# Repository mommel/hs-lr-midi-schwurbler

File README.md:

# Der Schwurbler

Happy Shooting Community - DIY Lightroom Hardware Controller

## Description
The german foto podcast legend Happy Shooting had a discussion about Midi controller for Lightroom. One comment on the website and voila a new project is born.
This project will (hopefully) contain everything from zero to hero to get create your own customized Midi Controller for Lightroom.
It is completly community driven, so everyone is allowed to contribute. And it's not intended to earn money with it. Just from the community for the community.
In general you might even need no case, just the pcb with the solded parts. so you will get an extra small extra lightwight device. If that's the thing for you we might even go the capacitive way and reduce the soldered components and weight to a minimum.

## MVP Video

<object width="425" height="350">
  <param name="movie" value="https://youtu.be/SjJDIjGQ-qA" />
  <param name="wmode" value="transparent" />
  <embed src="https://youtu.be/SjJDIjGQ-qA"
         type="application/x-shockwave-flash"
         wmode="transparent" width="425" height="350" />
</object>

https://youtu.be/SjJDIjGQ-qA

## WIKI
You can find our wiki here https://github.com/mommel/hs-lr-midi-schwurbler/wiki

## Status of the project
Released a version and onging development for next versions

### Tutorial
 *To be found soonish in the Wiki*

## Versions
### MVP
* based on Teensy 32bit boards
* USB Powered
* 10 + 4 Buttons
* 9 Poti

[BOM](https://hs-lr-midi-schwurbler.mommel.com/bom/schwurbler-mvp-1.2.ibom.html)

## Releases
* [MVP Version](https://github.com/mommel/hs-lr-midi-schwurbler/releases/tag/v1.0.0) released

## Help needed? F.A.Q.
* For support you can open an issue here on github.
* Maybe there will be a slack contact in the future.
* This project is a Happy Shooting _Community_ Project.
The best way to get help is joining the #der-schwurbler channel on the happyshooting slack. The community will do it's best and hopefully solve your issue.
* No hotline, no helpdesk. But we have something even greater: The Happy Shooting _Community_.

## How to contribute
* Fork, add, push, create a pull request
* create an issue on github
* You don't want to use Eagle, Kicad or Fritzing to create a layout. It's totally fine, as long the result can be used to create a PCB with no additional costs to the version created with the other software.

## How can I get one?
* Decide the version, take the Gerber Folder and bom.csv matching your decission. Upload the gerber Files to the manufacturer of your most trust. Mine are some even in china and even there is the delivery time below a week.

## License
* All layouts and diagrams are CC share alike non commercial attribution 4.0 licensed
So you can create and use them on your own even in your company, but you are not allowed to sell them.

<br />Dieses Werk ist lizenziert unter einer <a rel="license" href="http://creativecommons.org/licenses/by-nc-sa/4.0/">Creative Commons Namensnennung - Nicht-kommerziell - Weitergabe unter gleichen Bedingungen 4.0 International Lizenz</a>.
Namensnennung/Attribution to Happy Shooting Community https://happyshooting.de/community-projekte/

### Contributors in alphabetical order
chrismarquardt https://github.com/chrismarquardt
Mac ThreeZee https://github.com/MacThreeZee
Mommel https://github.com/mommel
Vielpixel https://github.com/Vielpixel
wolfgangSF https://github.com/wolfgangSF

# 3rd party licenses
External work have their own licenses and are covered or even touched by owner license.

## assets/SolderComics
* FullSolderComic_EN.pdf is licensed as https://creativecommons.org/licenses/by-sa/3.0 by Mitch Altmann, Andie Nordgren and Jeff Keyzer
* DE_SolderComic.pdf is licensed as https://creativecommons.org/licenses/by-sa/3.0 by Mitch Altmann, Andie Nordgren, Jeff Keyzer, Alexander Bodora and Richard Meinsen

## kicad/parts
### pretty _footprints_
_as submodule_
* XenGi_teensy.pretty is licensed under the MIT License by Ricardo Band
### lib _libraries_
_as submodule_
* XenGi_teensy_library is licensed under the MIT License by Ricardo Band

## Disclaimer
THE SOFTWARE IS PROVIDED "AS IS", WITHOUT WARRANTY OF ANY KIND, EXPRESS OR IMPLIED, INCLUDING BUT NOT LIMITED TO THE WARRANTIES OF MERCHANTABILITY, FITNESS FOR A PARTICULAR PURPOSE AND NONINFRINGEMENT. IN NO EVENT SHALL THE AUTHORS OR COPYRIGHT HOLDERS BE LIABLE FOR ANY CLAIM, DAMAGES OR OTHER LIABILITY, WHETHER IN AN ACTION OF CONTRACT, TORT OR OTHERWISE, ARISING FROM, OUT OF OR IN CONNECTION WITH THE SOFTWARE OR THE USE OR OTHER DEALINGS IN THE SOFTWARE.

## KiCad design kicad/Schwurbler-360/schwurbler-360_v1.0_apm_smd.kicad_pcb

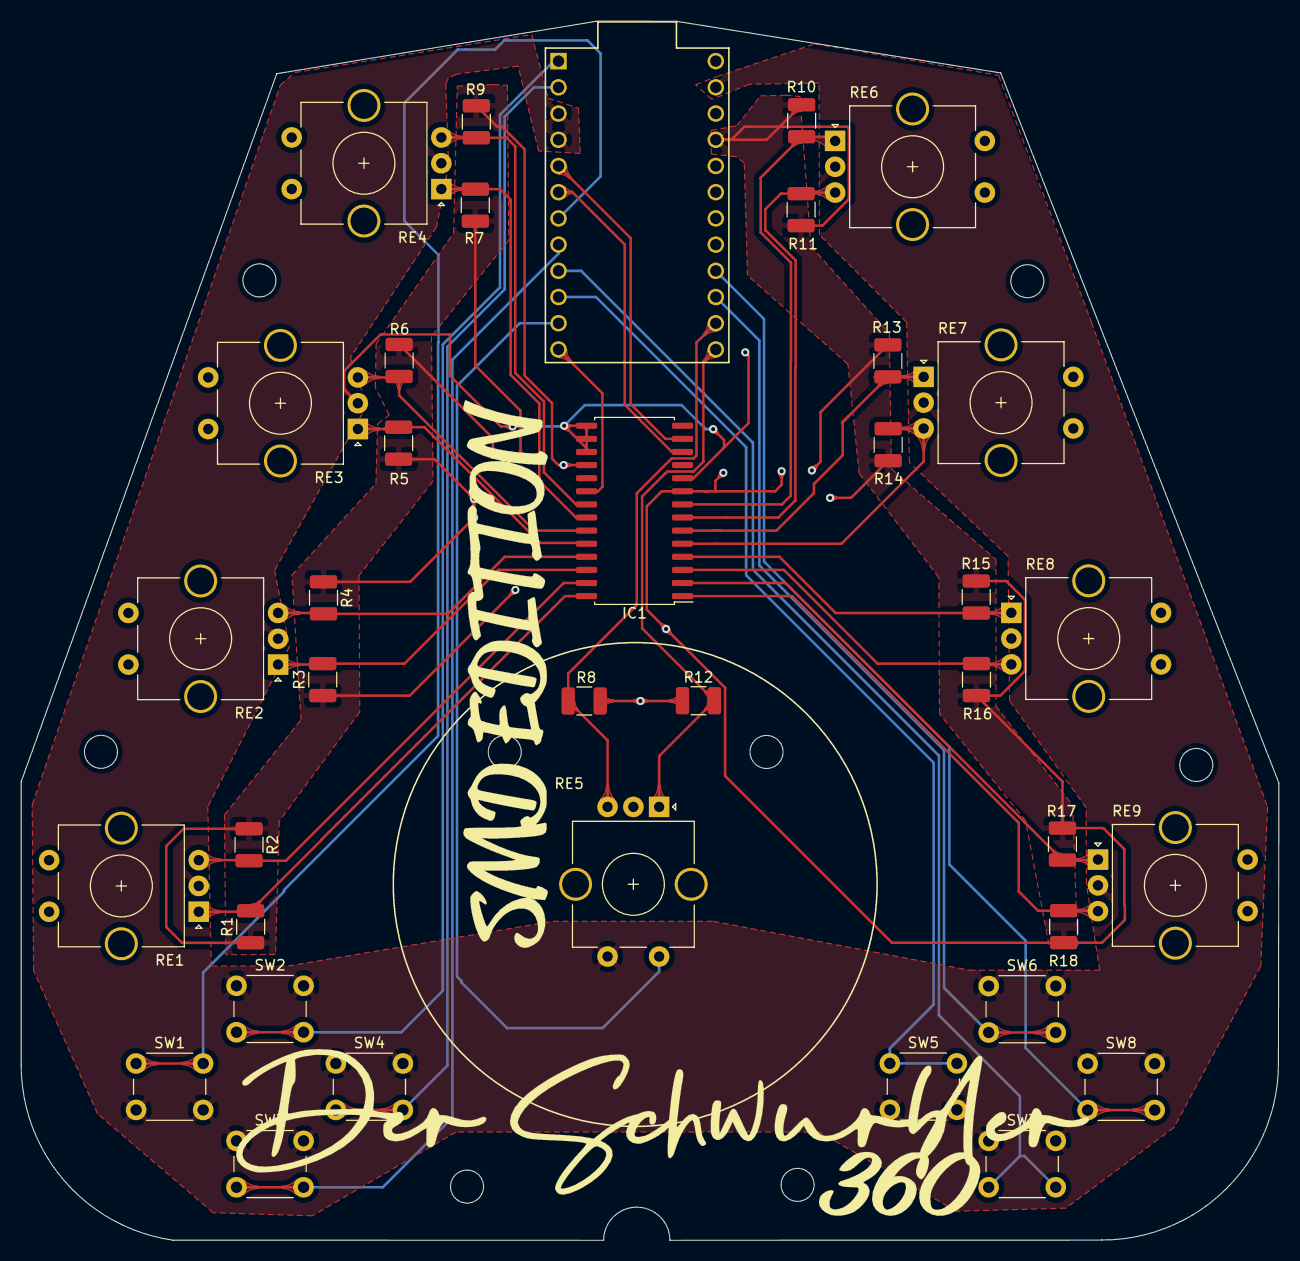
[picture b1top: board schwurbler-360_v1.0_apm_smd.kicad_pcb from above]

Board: 2 copper layers, 121.9 x 118.1 mm, 48 parts (1 on the bottom side), 32 nets.

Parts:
360logo: LOGO; 360
IC1: MCP23017_SO; SOIC-28W_7.5x17.9mm_P1.27mm
MCU1: ProMicro
MOUNTBCL: M3; MountingHole_3.2mm_M3
MOUNTBCR: M3; MountingHole_3.2mm_M3
MOUNTBL: M3; MountingHole_3.2mm_M3
MOUNTBR: M3; MountingHole_3.2mm_M3
MOUNTCML: M3; MountingHole_3.2mm_M3
MOUNTCMR: M3; MountingHole_3.2mm_M3
MOUNTTL: M3; MountingHole_3.2mm_M3
MOUNTTR: M3; MountingHole_3.2mm_M3
R1, R2, R3, R4, R5, R6, R7, R8, R9, R10, R11, R12, R13, R14, R15, R16, R17, R18: 10k; R_1210_3225Metric_Pad1.30x2.65mm_HandSolder
RE1, RE2, RE3, RE4, RE5, RE6, RE7, RE8, RE9: Rotary_Encoder_Switch; RotaryEncoder_Alps_EC11E-Switch_Vertical_H20mm_CircularMoun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
SW1, SW2, SW3, SW4, SW5, SW6, SW7, SW8: SW_Push; SW_PUSH_6mm_H5mm
cclogo: LOGO; ccbyncsa_o
smdlogo: LOGO; smdedition

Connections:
/5V: IC1.9, IC1.18, MCU1.21, R1.1, R2.1, R3.1, R4.1, R5.1, R6.1, R7.1, R8.1, R9.1, R10.1, R11.1, R12.1, R13.1, R14.1, R15.1, R16.1, R17.1, R18.1
/GND: IC1.10, IC1.15, IC1.16, IC1.17, MCU1.3, MCU1.4, MCU1.23, RE1.C, RE2.C, RE3.C, RE4.C, RE5.C, RE5.S1, RE6.C, RE7.C, RE8.C, RE9.C, SW1.2, SW2.1, SW3.1, SW4.1, SW5.2, SW6.1, SW7.1, SW8.1
/PWM: IC1.20, MCU1.12
/Push_1: MCU1.7, SW1.1
/Push_2: MCU1.1, SW2.2
/Push_3: MCU1.8, SW3.2
/Push_4: MCU1.2, SW4.2
/Push_5: MCU1.10, SW5.1
/Push_6: MCU1.15, SW6.2
/Push_7: MCU1.9, SW7.2
/Push_8: MCU1.16, SW8.2
/RE1_CLK: IC1.28, R1.2, RE1.A
/RE1_DT: IC1.27, R2.2, RE1.B
/RE2_CLK: IC1.26, R3.2, RE2.A
/RE2_DT: IC1.25, R4.2, RE2.B
/RE3_CLK: IC1.24, R5.2, RE3.A
/RE3_DT: IC1.23, R6.2, RE3.B
/RE4_CLK: IC1.22, R7.2, RE4.A
/RE4_DT: IC1.21, R9.2, RE4.B
/RE5_CLK: MCU1.14, R8.2, RE5.B
/RE5_DT: MCU1.13, R12.2, RE5.A
/RE6_CLK: IC1.8, R10.2, RE6.A
/RE6_DT: IC1.7, R11.2, RE6.B
/RE7_CLK: IC1.6, R13.2, RE7.A
/RE7_DT: IC1.5, R14.2, RE7.B
/RE8_CLK: IC1.4, R15.2, RE8.A
/RE8_DT: IC1.3, R16.2, RE8.B
/RE9_CLK: IC1.1, R18.2, RE9.B
/RE9_DT: IC1.2, R17.2, RE9.A
/RE_Push: MCU1.11, RE5.S2
/SCL: IC1.12, MCU1.6
/SDA: IC1.13, MCU1.5

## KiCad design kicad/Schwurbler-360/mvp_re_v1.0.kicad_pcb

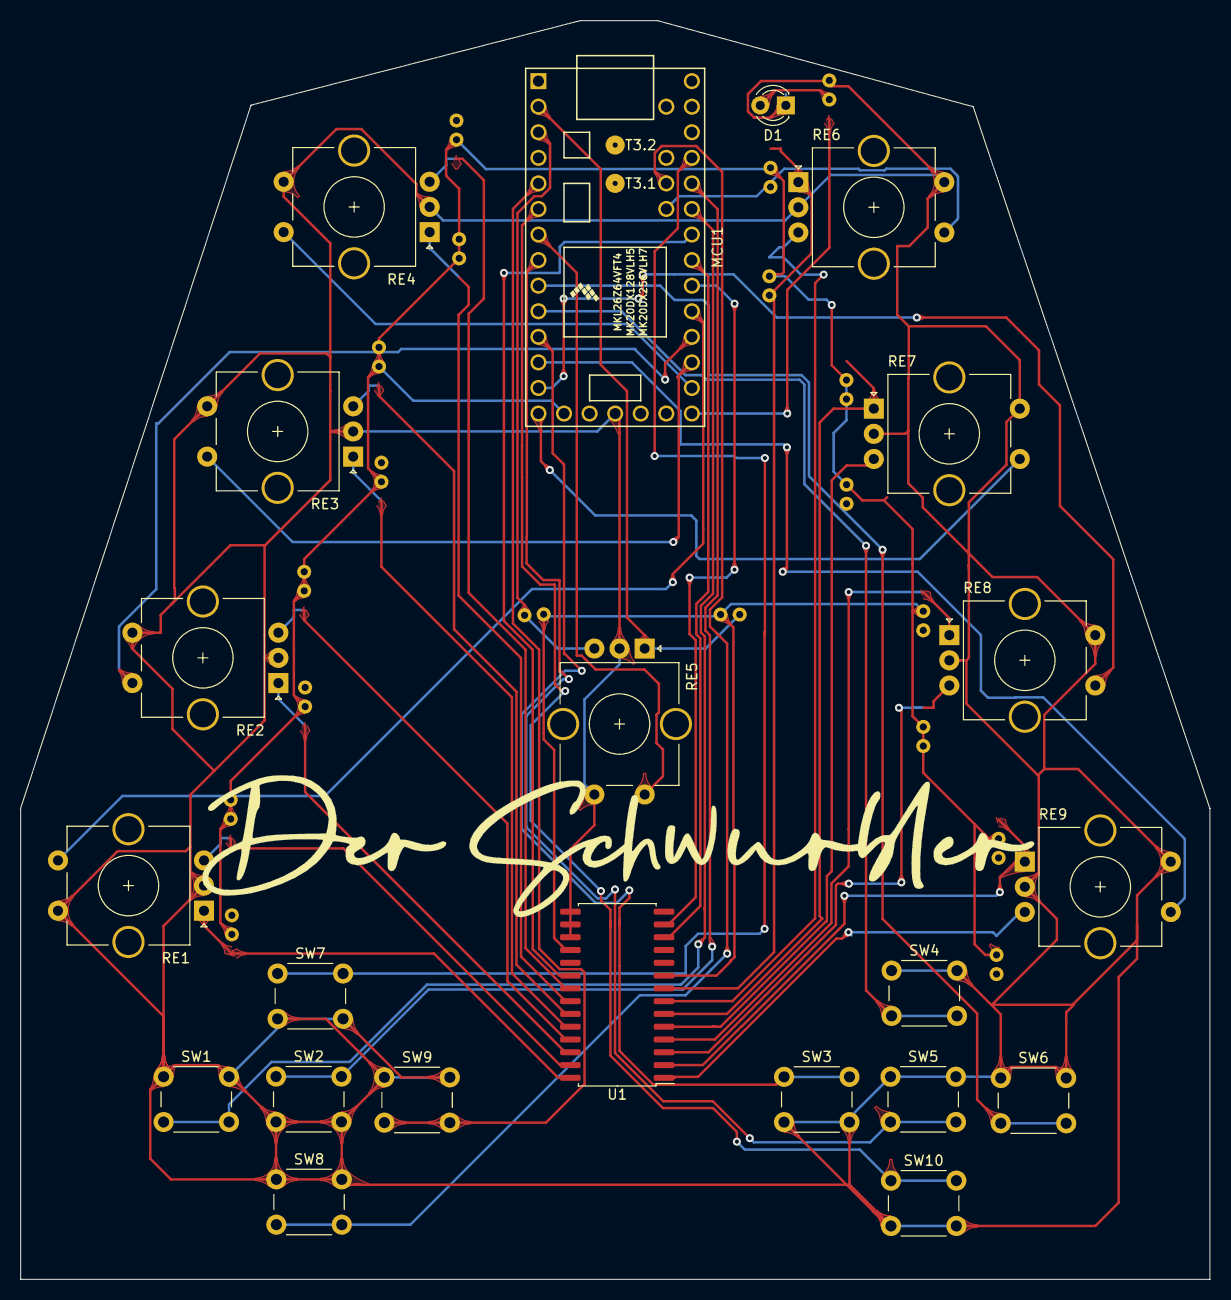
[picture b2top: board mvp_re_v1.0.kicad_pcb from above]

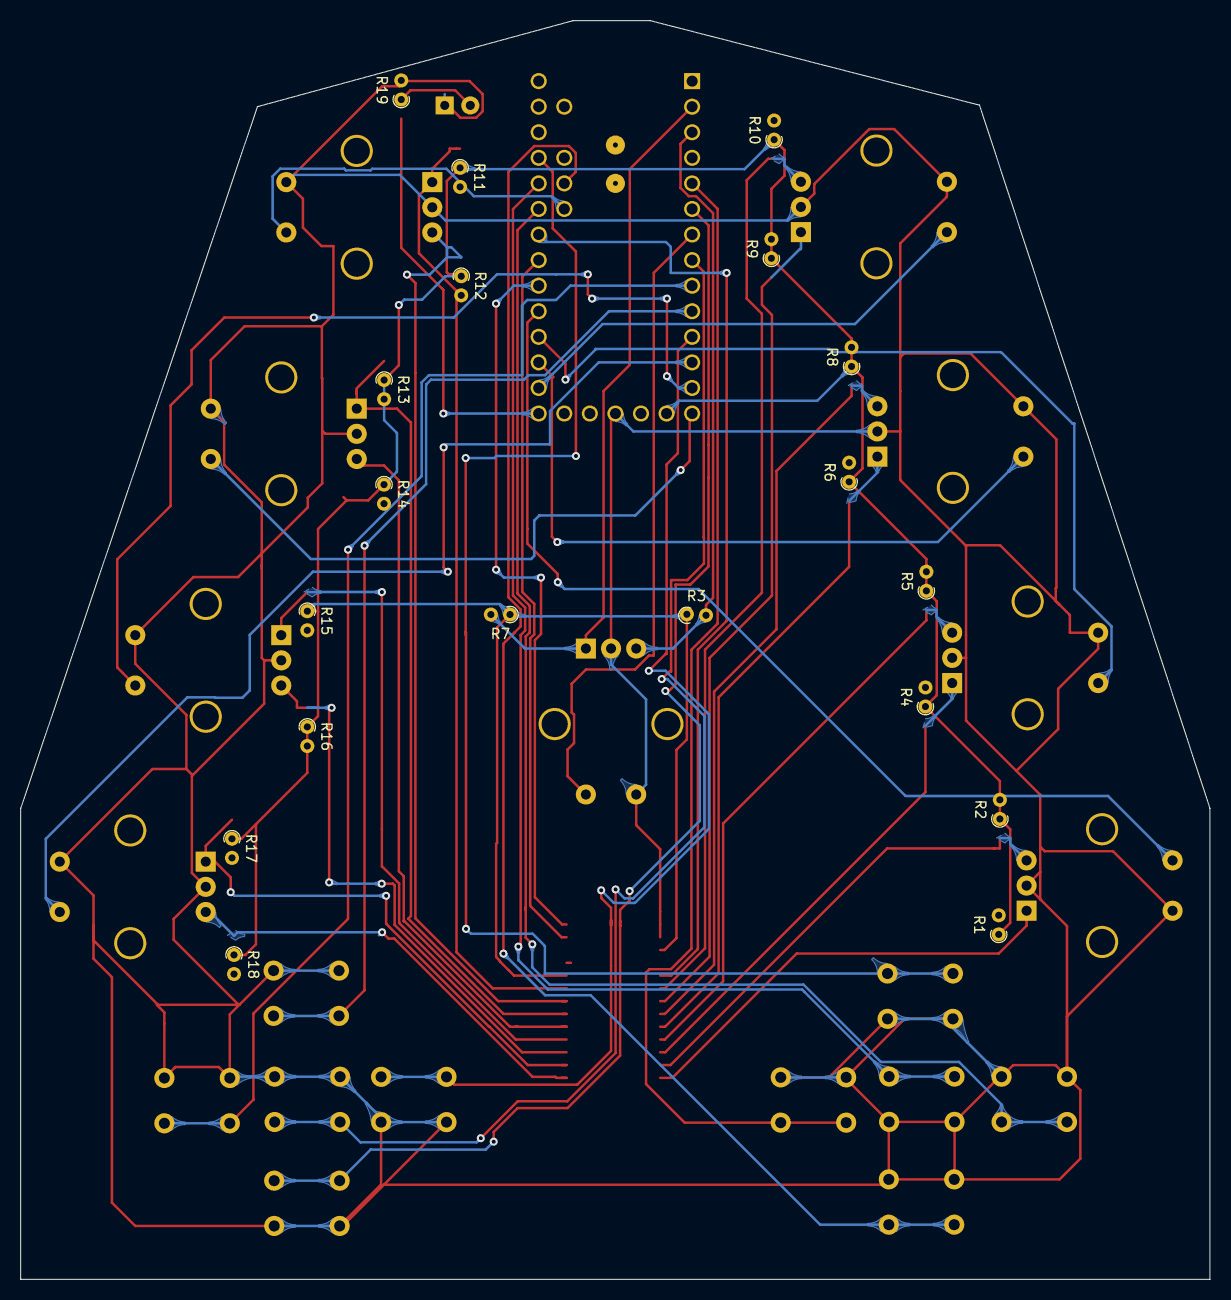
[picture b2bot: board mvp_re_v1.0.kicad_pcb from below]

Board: 2 copper layers, 118.1 x 125.0 mm, 41 parts (19 on the bottom side), 44 nets.

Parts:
D1: LED; LED_D3.0mm_FlatTop
MCU1: Teensy-LC; Teensy30_31_32_LC
R1, R2, R3, R4, R5, R6, R7, R8, R9, R10, R11, R12, R13, R14, R15, R16, R17, R18: 10k; R_Axial_DIN0204_L3.6mm_D1.6mm_P1.90mm_Vertical
R19: 330; R_Axial_DIN0204_L3.6mm_D1.6mm_P1.90mm_Vertical
RE1, RE2, RE3, RE4, RE5, RE6, RE7, RE8, RE9: Rotary_Encoder_Switch; RotaryEncoder_Alps_EC11E-Switch_Vertical_H20mm_CircularMoun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
SW1, SW2, SW3, SW4, SW5, SW6, SW7, SW8, SW9, SW10: SW_Push; SW_PUSH_6mm_H5mm
U1: MCP23017_SS; SOIC-28W_7.5x17.9mm_P1.27mm

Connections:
/5V: MCU1.15, R1.1, R2.1, R3.1, R4.1, R5.1, R6.1, R7.1, R8.1, R9.1, R10.1, R11.1, R12.1, R13.1, R14.1, R15.1, R16.1, R17.1, R18.1, U1.9, U1.18
/GND: D1.1, MCU1.17, RE1.C, RE1.S2, RE2.C, RE2.S1, RE3.C, RE3.S1, RE4.C, RE4.S1, RE5.C, RE5.S1, RE6.C, RE6.S2, RE7.C, RE7.S2, RE8.C, RE8.S2, RE9.C, RE9.S2, SW1.1, SW2.2, SW3.2, SW4.1, SW5.1, SW6.1, SW7.2, SW8.1, SW9.1, SW10.2, U1.10, U1.15, U1.16, U1.17
/PWM: MCU1.27, U1.20
/SCL: MCU1.26, U1.12
/SDA: MCU1.25, U1.13
unnamed: D1.2, R19.1
unnamed: MCU1.2, R7.2, RE5.A
unnamed: MCU1.3, R3.2, RE5.B
unnamed: MCU1.5, SW9.2
unnamed: MCU1.6, SW10.1
unnamed: MCU1.7, RE5.S2
unnamed: MCU1.8, SW5.2
unnamed: MCU1.9, SW6.2
unnamed: MCU1.10, SW4.2
unnamed: MCU1.11, SW3.1
unnamed: MCU1.12, RE9.S1
unnamed: MCU1.13, RE8.S1
unnamed: MCU1.14, RE7.S1
unnamed: MCU1.20, R19.2
unnamed: MCU1.21, RE4.S2
unnamed: MCU1.22, RE3.S2
unnamed: MCU1.23, RE2.S2
unnamed: MCU1.24, RE1.S1
unnamed: MCU1.28, SW1.2
unnamed: MCU1.29, SW2.1
unnamed: MCU1.30, SW7.1
unnamed: MCU1.36, SW8.2
unnamed: MCU1.37, RE6.S1
unnamed: R1.2, RE1.A, U1.28
unnamed: R2.2, RE1.B, U1.27
unnamed: R4.2, RE2.A, U1.26
unnamed: R5.2, RE2.B, U1.25
unnamed: R6.2, RE3.A, U1.24
unnamed: R8.2, RE3.B, U1.23
unnamed: R9.2, RE4.A, U1.22
unnamed: R10.2, RE4.B, U1.21
unnamed: R11.2, RE6.A, U1.8
unnamed: R12.2, RE6.B, U1.7
unnamed: R13.2, RE7.A, U1.6
unnamed: R14.2, RE7.B, U1.5
unnamed: R15.2, RE8.A, U1.4
unnamed: R16.2, RE8.B, U1.3
unnamed: R17.2, RE9.A, U1.2
unnamed: R18.2, RE9.B, U1.1

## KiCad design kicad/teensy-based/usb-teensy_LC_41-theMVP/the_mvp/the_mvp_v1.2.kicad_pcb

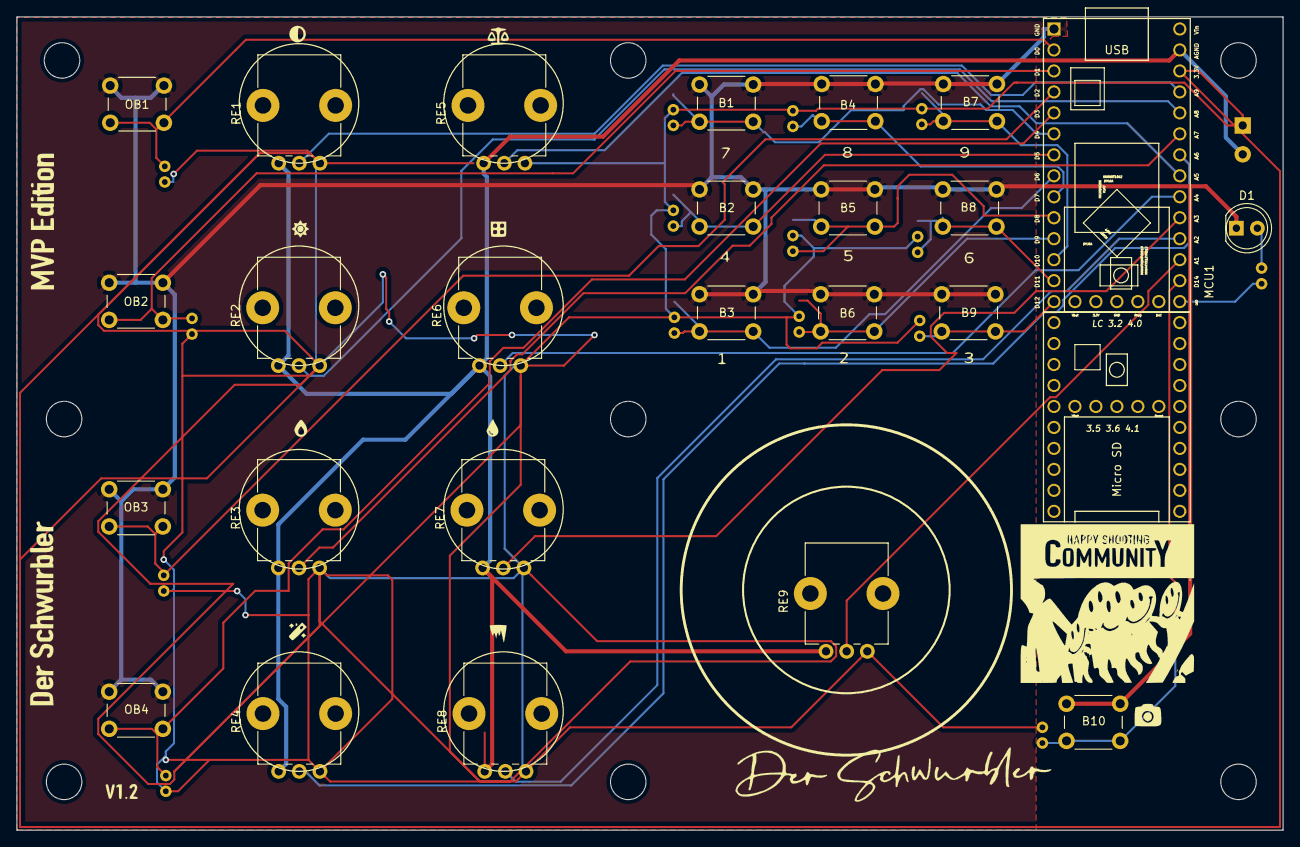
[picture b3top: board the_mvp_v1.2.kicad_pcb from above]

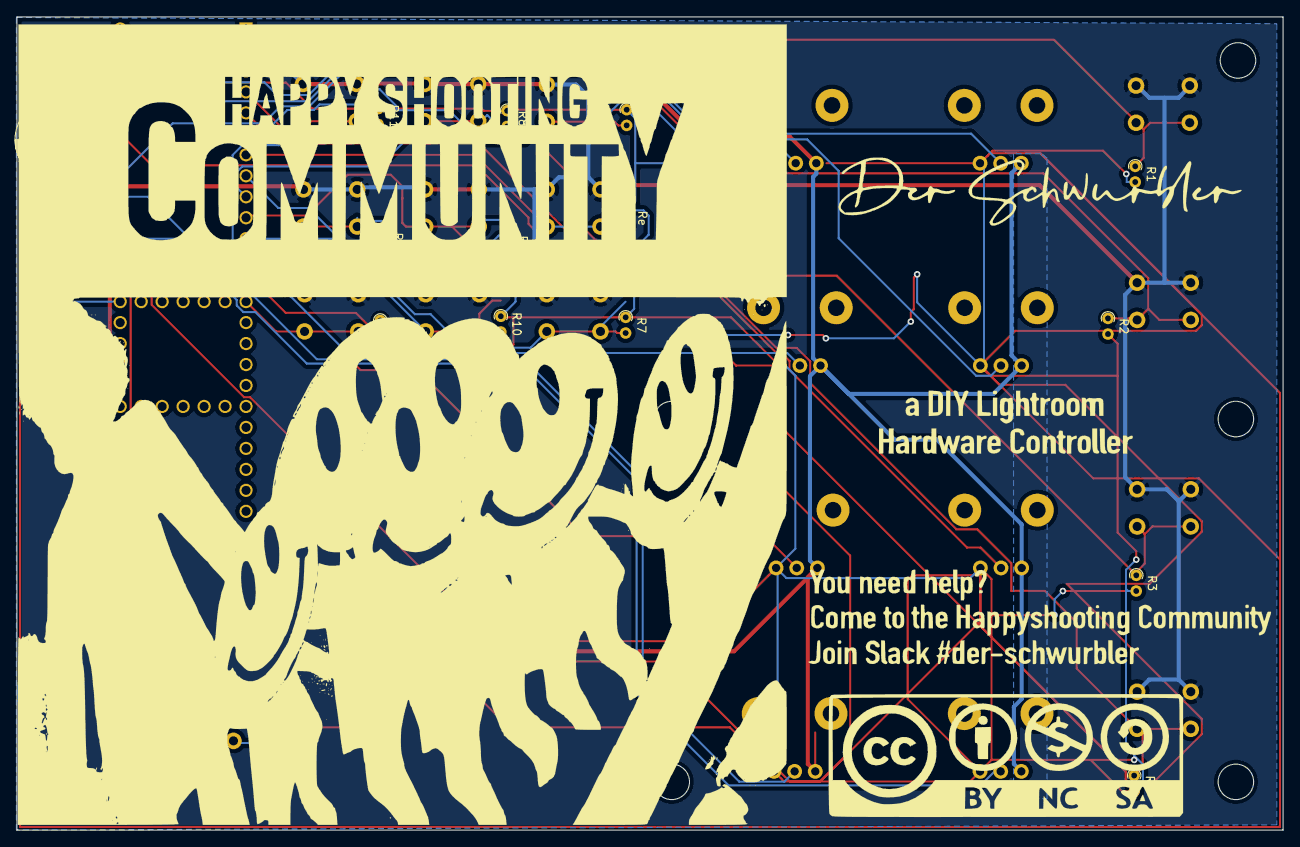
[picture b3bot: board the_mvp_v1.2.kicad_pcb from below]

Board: 2 copper layers, 153.4 x 98.5 mm, 50 parts (16 on the bottom side), 28 nets.

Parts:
B1, B2, B3, B4, B5, B6, B7, B8, B9, B10: monumentary switch Buttons; SW_PUSH_6mm_H5mm
C1: optional; CP_Radial_D10.0mm_P3.50mm
D1: LED; LED_D5.0mm
MCU1: Teensy4.1; Teensy_Schwurbler_Unified_Footprint
MHBC: MountingHole_4.3mm_M4
MHBL: MountingHole_4.3mm_M4
MHBR: MountingHole_4.3mm_M4
MHMC: MountingHole_4.3mm_M4
MHML: MountingHole_4.3mm_M4
MHMR: MountingHole_4.3mm_M4
MHTC: MountingHole_4.3mm_M4
MHTL: MountingHole_4.3mm_M4
MHTR: MountingHole_4.3mm_M4
OB1: optional monumentary switch Buttons; SW_PUSH_6mm_H5mm
OB2, OB3, OB4: monumentary switch Button; SW_PUSH_6mm_H5mm
R1, R2, R3, R4, R5, R7, R8, R9, R10, R11, R12, R13, R14: 10kOhm (optional); R_Axial_DIN0204_L3.6mm_D1.6mm_P1.90mm_Vertical
R15: 470Ohm (optional); R_Axial_DIN0204_L3.6mm_D1.6mm_P1.90mm_Vertical
RE1, RE2, RE3, RE4, RE5, RE6, RE7, RE8, RE9: 10k; Potentiometer_Alps_RK09K_Single_Vertical
Re: 10kOhm (optional); R_Axial_DIN0204_L3.6mm_D1.6mm_P1.90mm_Vertical

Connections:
GND: B1.1, B2.1, B3.1, B4.1, B5.1, B6.1, B7.1, B8.1, B9.1, B10.1, D1.1, MCU1.1, OB1.1, OB2.1, OB3.1, OB4.1
unnamed: B1.2, MCU1.6, R5.2
unnamed: B2.2, MCU1.7, Re.2
unnamed: B3.2, MCU1.8, R7.2
unnamed: B4.2, MCU1.9, R8.2
unnamed: B5.2, MCU1.10, R9.2
unnamed: B6.2, MCU1.11, R10.2
unnamed: B7.2, MCU1.12, R11.2
unnamed: B8.2, MCU1.13, R12.2
unnamed: B9.2, MCU1.14, R13.2
unnamed: B10.2, MCU1.36, R14.2
unnamed: C1.1, MCU1.46, R1.2, R2.2, R3.2, R4.2, R5.1, R7.1, R8.1, R9.1, R10.1, R11.1, R12.1, R13.1, R14.1, RE1.1, RE2.1, RE3.1, RE4.1, RE5.1, RE6.1, RE7.1, RE8.1, RE9.1, Re.1
unnamed: C1.2, MCU1.47, RE1.3, RE2.3, RE3.3, RE4.3, RE5.3, RE6.3, RE7.3, RE8.3, RE9.3
unnamed: D1.2, R15.1
unnamed: MCU1.2, OB1.2, R1.1
unnamed: MCU1.3, OB2.2, R2.1
unnamed: MCU1.4, OB3.2, R3.1
unnamed: MCU1.5, OB4.2, R4.1
unnamed: MCU1.35, R15.2
unnamed: MCU1.37, RE9.2
unnamed: MCU1.38, RE8.2
unnamed: MCU1.39, RE7.2
unnamed: MCU1.40, RE6.2
unnamed: MCU1.41, RE5.2
unnamed: MCU1.42, RE4.2
unnamed: MCU1.43, RE3.2
unnamed: MCU1.44, RE2.2
unnamed: MCU1.45, RE1.2

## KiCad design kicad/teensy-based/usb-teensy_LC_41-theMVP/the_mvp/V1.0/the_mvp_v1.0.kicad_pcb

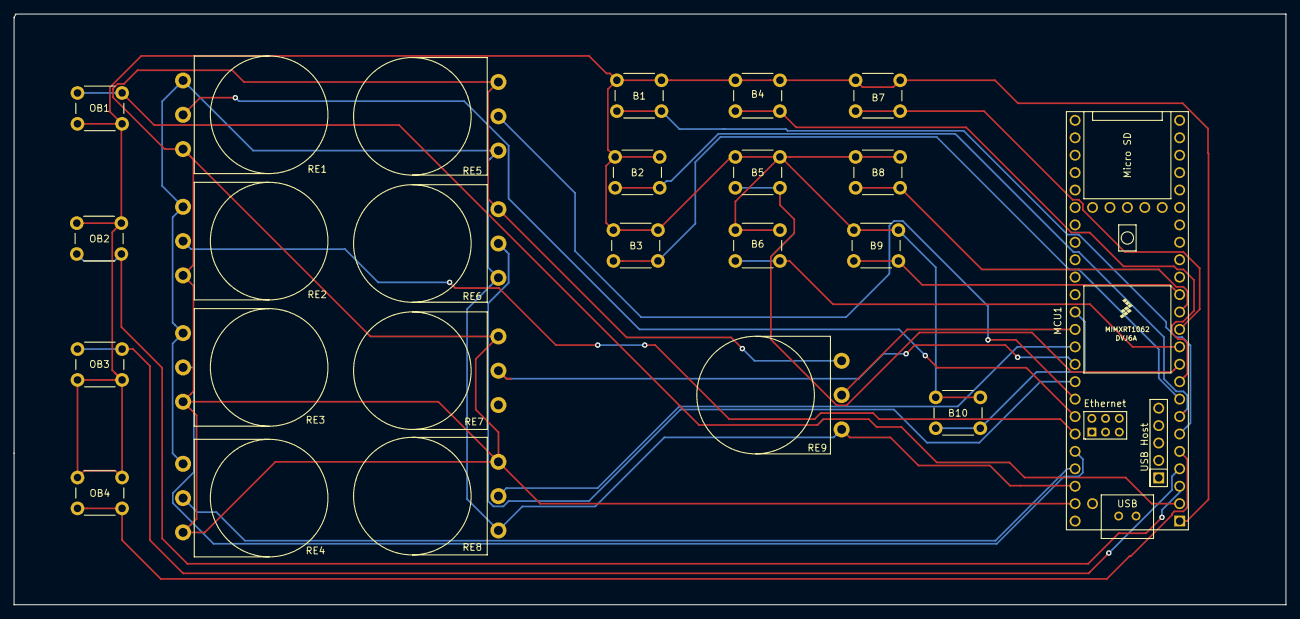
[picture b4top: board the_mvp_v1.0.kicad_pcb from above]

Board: 2 copper layers, 185.4 x 86.1 mm, 24 parts (0 on the bottom side), 13 nets.

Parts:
B1, B2, B3, B4, B5, B6, B7, B8, B9, B10: monumentary switch Buttons; SW_PUSH_6mm_H5mm
MCU1: Teensy4.1; Teensy41
OB1: optional monumentary switch Buttons; SW_PUSH_6mm_H5mm
OB2, OB3, OB4: monumentary switch Button; SW_PUSH_6mm_H5mm
RE1, RE2, RE3, RE4, RE5, RE6, RE7, RE8, RE9: 10k; Potentiometer_Omeg_PC16BU_Vertical

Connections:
GND: B1.1, B2.1, B3.1, B4.1, B5.1, B6.1, B7.1, B8.1, B9.1, B10.1, MCU1.1, OB1.1, OB2.1, OB3.1, OB4.1
unnamed: B1.2, MCU1.6
unnamed: B2.2, MCU1.7
unnamed: B3.2, MCU1.8
unnamed: B4.2, MCU1.9
unnamed: B5.2, MCU1.10
unnamed: B6.2, MCU1.11
unnamed: B7.2, MCU1.12
unnamed: B8.2, MCU1.13
unnamed: B9.2, MCU1.14
unnamed: B10.2, MCU1.36
unnamed: MCU1.2, OB1.2
unnamed: MCU1.5, OB4.2

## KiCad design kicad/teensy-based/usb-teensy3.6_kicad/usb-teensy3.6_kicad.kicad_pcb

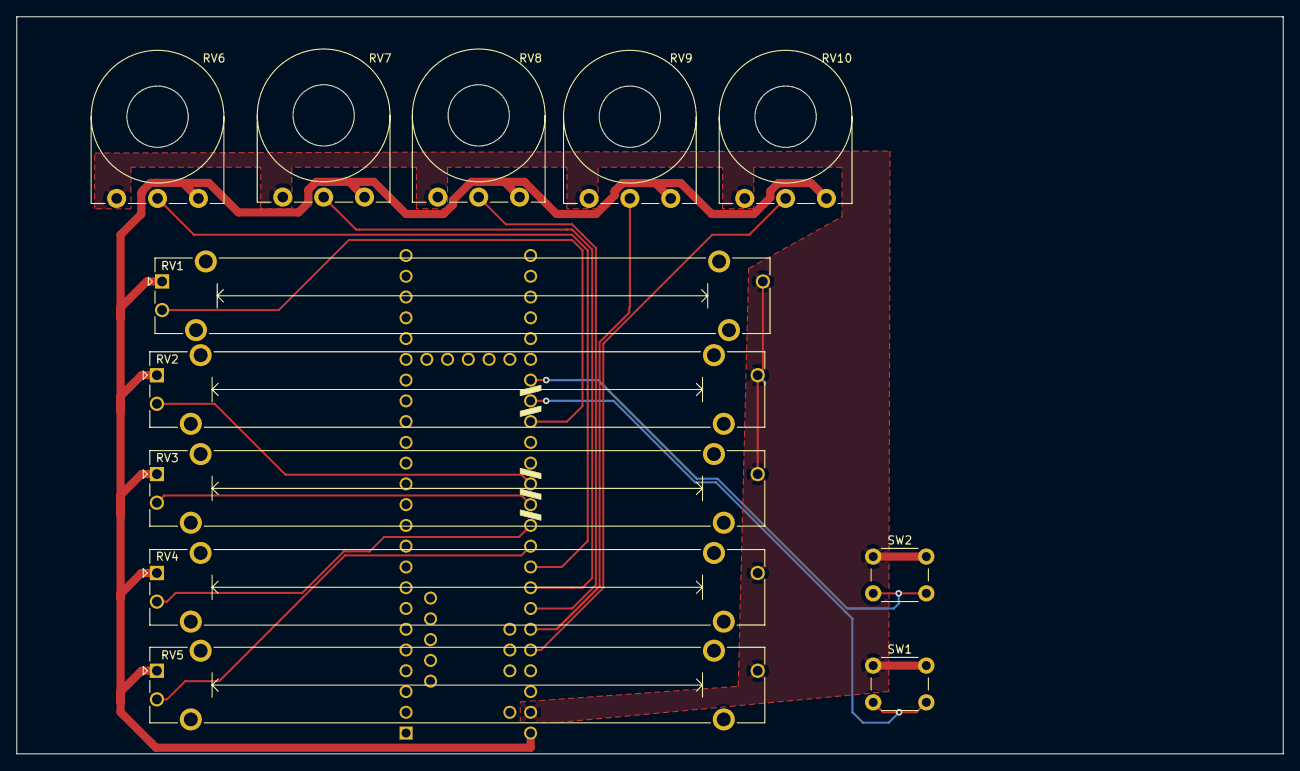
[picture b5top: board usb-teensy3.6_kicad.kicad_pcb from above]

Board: 2 copper layers, 154.9 x 90.2 mm, 13 parts (1 on the bottom side), 14 nets.

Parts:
RV1, RV2, RV3, RV4, RV5: 10k sl; Potentiometer_Bourns_PTA6043_Single_Slide
RV6, RV7, RV8, RV9, RV10: 10k ro; Potentiometer_Piher_T-16L_Single_Vertical_Hole
SW1, SW2: SW_Push; SW_PUSH_6mm_H8mm
U1: Teensy3.6; Teensy36

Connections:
GND: RV1.3, RV2.3, RV3.3, RV4.3, RV5.3, RV6.3, RV7.3, RV8.3, RV9.3, RV10.3, SW1.1, SW2.1, U1.52
unnamed: RV1.1, RV2.1, RV3.1, RV4.1, RV5.1, RV6.1, RV7.1, RV8.1, RV9.1, RV10.1, U1.53
unnamed: RV1.2, U1.38
unnamed: RV2.2, U1.41
unnamed: RV3.2, U1.42
unnamed: RV4.2, U1.43
unnamed: RV5.2, U1.44
unnamed: RV6.2, U1.45
unnamed: RV7.2, U1.46
unnamed: RV8.2, U1.47
unnamed: RV9.2, U1.48
unnamed: RV10.2, U1.49
unnamed: SW1.2, U1.37
unnamed: SW2.2, U1.36

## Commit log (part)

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2020-08-01 First glympse of a board for Teensy 3.6
2020-08-01 adds one image to readme
2020-08-04 minor change in wording need help
2020-08-04 mod render without parts
2020-08-04 fixing potis
2020-08-04 update pcb with alternative layout
2020-08-07 Adds untested code
2020-08-10 adds unix helper scipt
    The helper script has following functions:
    new) create a new branch with a skeleton folder structure for a new board
    pack) packs all files matching to the selected board together in one archive
    // If you are not so familar with git
    branch) switch the branch
    add2git) add files to to git
2020-08-11 adds LICENSE file
2020-08-13 mods teensy3.6 untested example code to be compilable
    adds arrayCount function
    fixes quotes for Serial string
    homogenizes variable name for midi Channel
2020-08-19 adds design-drafts folder
2020-08-19 removes outdated & adds informations to readme
2020-08-23 adds pcb, gerber, schema, etching
2020-08-26 adds versioning to kicad filenames
2020-08-26 copies 1.0 schema to 1.1
2020-08-26 add wiki as submodule
2020-08-27 Update issue templates
2020-09-01 Add files via upload
    zweiter Versuch
2020-09-05 adds src file of quickstartguide de and gitattr for psd
2020-09-05 adds en version of quickstartguide
2020-09-08 removes lfs files
2020-09-09 New images for the images-wiki folder
2020-09-10 adds function to deal with return channel
2020-09-10 modifes pcb to fix issues from v1.1
2020-09-10 adds etchingprint
2020-09-13 moving and removing everything
2020-09-14 Bilder für den images-wiki Folder
    Ich hab hier noch das neue 3-d Gehäuse und ein paar bessere Bilder fürs Wiki.
2020-09-15 moving midi2lr stuff in own folder
2020-09-25 adds cppcheck lintcheck + reformats code
2020-10-03 adds the base for a ble version
2020-10-04 moved amount values to buildtime constants
2020-10-10 creates empty folder structure for code
2020-10-12 Move folder one step up
2020-10-12 updates env
2020-10-12 Test automerge rules working as intended
2020-10-12 Test if checks are now running
2020-10-14 splits controller from main code adds some unready tests
2020-10-14 Housekeeping the git ignores
2020-10-14 Incomplete but nice
2020-10-15 add clang tidy review, mods cpplint
2020-10-15 adds other Versions to master
2020-10-16 modifies docs generation action
2020-10-16 modifies doc generation action
2020-10-16 remove unneeded stuff from actions
2020-10-16 Housekeeping the git ignores
    # Conflicts:
    # .gitignore
    # Conflicts:
    # .gitignore
2020-10-16 fix wrong branch
2020-10-16 adds origin to rebase master action
2020-10-16 rm the upstream from action
2020-10-17 updates follow workflow
2020-10-23 Add files via upload
    These are the new Midi2LR Profiles for Lightroom 10. Added support for the new Color Grading feature in Lightroom 10.
2020-10-27 Adds multilang generator for wikipages
    makefile for Win only, will add make version later
    creates the base for the auto code explaination to the wiki
    need to still have an eye on direct wiki changes to end in the right src files
2020-10-27 adds submodule with actual wiki content
2020-10-28 addds doc generation
2020-10-28 fix findings
2020-10-30 Adds 'real' Makefile for Wiki autogen
2020-11-19 adds code, schematics and pcb
2020-11-19 removes unused github actions
    * docs will be generated in controllers project
    * master follow did not work good enough
2020-11-20 adds smd edition
2020-11-20 add prototyping
2021-01-22 Bump lxml from 4.6.1 to 4.6.2 in /code/Utilities (#63)
    Bumps [lxml](https://github.com/lxml/lxml) from 4.6.1 to 4.6.2.
    - [Release notes](https://github.com/lxml/lxml/releases)
    - [Changelog](https://github.com/lxml/lxml/blob/master/CHANGES.txt)
    - [Commits](https://github.com/lxml/lxml/compare/lxml-4.6.1...lxml-4.6.2)
2021-03-20 Bump jinja2 from 2.11.2 to 2.11.3 in /code/Utilities
    Bumps [jinja2](https://github.com/pallets/jinja) from 2.11.2 to 2.11.3.
    - [Release notes](https://github.com/pallets/jinja/releases)
    - [Changelog](https://github.com/pallets/jinja/blob/master/CHANGES.rst)
    - [Commits](https://github.com/pallets/jinja/compare/2.11.2...2.11.3)
2021-03-21 Bump jinja2 from 2.11.2 to 2.11.3 in /code/Utilities (#65)
2021-03-30 Bump pygments from 2.7.2 to 2.7.4 in /code/Utilities
    Bumps [pygments](https://github.com/pygments/pygments) from 2.7.2 to 2.7.4.
    - [Release notes](https://github.com/pygments/pygments/releases)
    - [Changelog](https://github.com/pygments/pygments/blob/master/CHANGES)
    - [Commits](https://github.com/pygments/pygments/compare/2.7.2...2.7.4)
2021-04-05 fixes following findings
    # lxml
    CVE-2021-28957
    moderate severity
    Vulnerable versions: < 4.6.3
    Patched version: 4.6.3
    An XSS vulnerability was discovered in the python lxml clean module versions before 4.6.3. When disabling the safe_attrs_only and forms arguments, the Cleaner class does not remove the formaction att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
2021-05-09 Bump handlebars from 4.7.6 to 4.7.7 in /code/Utilities
    Bumps [handlebars](https://github.com/wycats/handlebars.js) from 4.7.6 to 4.7.7.
    - [Release notes](https://github.com/wycats/handlebars.js/releases)
    - [Changelog](https://github.com/handlebars-lang/handlebars.js/blob/master/release-notes.md)
    - [Commits](https://github.com/wycats/handlebars.js/compare/v4.7.6...v4.7.7)
2021-06-02 Bump urllib3 from 1.25.11 to 1.26.5 in /code/Utilities
    Bumps [urllib3](https://github.com/urllib3/urllib3) from 1.25.11 to 1.26.5.
    - [Release notes](https://github.com/urllib3/urllib3/releases)
    - [Changelog](https://github.com/urllib3/urllib3/blob/main/CHANGES.rst)
    - [Commits](https://github.com/urllib3/urllib3/compare/1.25.11...1.26.5)
    ---
    updated-dependencies:
2021-09-10 Bump urllib3 from 1.25.11 to 1.26.5 in /code/Utilities (#71)
    Bumps [urllib3](https://github.com/urllib3/urllib3) from 1.25.11 to 1.26.5.
    - [Release notes](https://github.com/urllib3/urllib3/releases)
    - [Changelog](https://github.com/urllib3/urllib3/blob/main/CHANGES.rst)
    - [Commits](https://github.com/urllib3/urllib3/compare/1.25.11...1.26.5)
    ---
    updated-dependencies:
2021-10-21 Bump babel from 2.8.0 to 2.9.1 in /code/Utilities
    Bumps [babel](https://github.com/python-babel/babel) from 2.8.0 to 2.9.1.
    - [Release notes](https://github.com/python-babel/babel/releases)
    - [Changelog](https://github.com/python-babel/babel/blob/master/CHANGES)
    - [Commits](https://github.com/python-babel/babel/compare/v2.8.0...v2.9.1)
    ---
    updated-dependencies:
2022-02-14 Add files via upload
    Fixed connections to Pins 1, 11, 12, 13 and 23 of the Arduino Pro Micro.
2022-11-10 Bump minimatch from 3.0.4 to 3.1.2 in /code/Utilities
    Bumps [minimatch](https://github.com/isaacs/minimatch) from 3.0.4 to 3.1.2.
    - [Release notes](https://github.com/isaacs/minimatch/releases)
    - [Commits](https://github.com/isaacs/minimatch/compare/v3.0.4...v3.1.2)
    ---
    updated-dependencies:
    - dependency-name: minimatch
2022-12-08 Bump certifi from 2020.6.20 to 2022.12.7 in /code/Utilities
    Bumps [certifi](https://github.com/certifi/python-certifi) from 2020.6.20 to 2022.12.7.
    - [Release notes](https://github.com/certifi/python-certifi/releases)
    - [Commits](https://github.com/certifi/python-certifi/compare/2020.06.20...2022.12.07)
    ---
    updated-dependencies:
    - dependency-name: certifi
2025-12-05 Bump urllib3 from 1.26.5 to 2.6.0 in /code/Utilities
    Bumps [urllib3](https://github.com/urllib3/urllib3) from 1.26.5 to 2.6.0.
    - [Release notes](https://github.com/urllib3/urllib3/releases)
    - [Changelog](https://github.com/urllib3/urllib3/blob/main/CHANGES.rst)
    - [Commits](https://github.com/urllib3/urllib3/compare/1.26.5...2.6.0)
    ---
    updated-dependencies:
2026-01-07 Bump urllib3 from 1.26.5 to 2.6.3 in /code/Utilities
    Bumps [urllib3](https://github.com/urllib3/urllib3) from 1.26.5 to 2.6.3.
    - [Release notes](https://github.com/urllib3/urllib3/releases)
    - [Changelog](https://github.com/urllib3/urllib3/blob/main/CHANGES.rst)
    - [Commits](https://github.com/urllib3/urllib3/compare/1.26.5...2.6.3)
    ---
    updated-dependencies:
2026-01-31 Bump requests from 2.24.0 to 2.32.4 in /code/Utilities
    Bumps [requests](https://github.com/psf/requests) from 2.24.0 to 2.32.4.
    - [Release notes](https://github.com/psf/requests/releases)
    - [Changelog](https://github.com/psf/requests/blob/main/HISTORY.md)
    - [Commits](https://github.com/psf/requests/compare/v2.24.0...v2.32.4)
    ---
    updated-dependencies:
2026-01-31 Bump tornado from 6.0.4 to 6.5 in /code/Utilities
    Bumps [tornado](https://github.com/tornadoweb/tornado) from 6.0.4 to 6.5.
    - [Changelog](https://github.com/tornadoweb/tornado/blob/master/docs/releases.rst)
    - [Commits](https://github.com/tornadoweb/tornado/compare/v6.0.4...v6.5.0)
    ---
    updated-dependencies:
    - dependency-name: tornado
2026-01-31 Bump brace-expansion from 1.1.11 to 1.1.12 in /code/Utilities
    Bumps [brace-expansion](https://github.com/juliangruber/brace-expansion) from 1.1.11 to 1.1.12.
    - [Release notes](https://github.com/juliangruber/brace-expansion/releases)
    - [Commits](https://github.com/juliangruber/brace-expansion/compare/1.1.11...v1.1.12)
    ---
    updated-dependencies:
    - dependency-name: brace-expansion
2026-03-06 Bump markdown from 3.3.3 to 3.8.1 in /code/Utilities
    Bumps [markdown](https://github.com/Python-Markdown/markdown) from 3.3.3 to 3.8.1.
    - [Release notes](https://github.com/Python-Markdown/markdown/releases)
    - [Changelog](https://github.com/Python-Markdown/markdown/blob/master/docs/changelog.md)
    - [Commits](https://github.com/Python-Markdown/markdown/compare/3.3.3...3.8.1)
    ---
    updated-dependencies:
2026-03-12 Bump black from 19.10b0 to 26.3.1 in /wiki
    Bumps [black](https://github.com/psf/black) from 19.10b0 to 26.3.1.
    - [Release notes](https://github.com/psf/black/releases)
    - [Changelog](https://github.com/psf/black/blob/main/CHANGES.md)
    - [Commits](https://github.com/psf/black/commits/26.3.1)
    ---
    updated-dependencies:
2026-03-27 Bump handlebars from 4.7.7 to 4.7.9 in /code/Utilities
    Bumps [handlebars](https://github.com/handlebars-lang/handlebars.js) from 4.7.7 to 4.7.9.
    - [Release notes](https://github.com/handlebars-lang/handlebars.js/releases)
    - [Changelog](https://github.com/handlebars-lang/handlebars.js/blob/v4.7.9/release-notes.md)
    - [Commits](https://github.com/handlebars-lang/handlebars.js/compare/v4.7.7...v4.7.9)
    ---
    updated-dependencies:
2026-04-25 Bump gitpython from 3.1.11 to 3.1.47 in /code/Utilities
    Bumps [gitpython](https://github.com/gitpython-developers/GitPython) from 3.1.11 to 3.1.47.
    - [Release notes](https://github.com/gitpython-developers/GitPython/releases)
    - [Changelog](https://github.com/gitpython-developers/GitPython/blob/main/CHANGES)
    - [Commits](https://github.com/gitpython-developers/GitPython/compare/3.1.11...3.1.47)
    ---
    updated-dependencies:
2026-05-09 Bump brace-expansion from 1.1.11 to 1.1.14 in /code/Utilities
    Bumps [brace-expansion](https://github.com/juliangruber/brace-expansion) from 1.1.11 to 1.1.14.
    - [Release notes](https://github.com/juliangruber/brace-expansion/releases)
    - [Commits](https://github.com/juliangruber/brace-expansion/compare/1.1.11...v1.1.14)
    ---
    updated-dependencies:
    - dependency-name: brace-expansion
2026-05-19 Bump idna from 2.10 to 3.15 in /code/Utilities
    Bumps [idna](https://github.com/kjd/idna) from 2.10 to 3.15.
    - [Release notes](https://github.com/kjd/idna/releases)
    - [Changelog](https://github.com/kjd/idna/blob/master/HISTORY.md)
    - [Commits](https://github.com/kjd/idna/compare/v2.10...v3.15)
    ---
    updated-dependencies:
2026-06-16 Bump tornado from 6.0.4 to 6.5.7 in /code/Utilities
    Bumps [tornado](https://github.com/tornadoweb/tornado) from 6.0.4 to 6.5.7.
    - [Changelog](https://github.com/tornadoweb/tornado/blob/master/docs/releases.rst)
    - [Commits](https://github.com/tornadoweb/tornado/compare/v6.0.4...v6.5.7)
    ---
    updated-dependencies:
    - dependency-name: tornado
